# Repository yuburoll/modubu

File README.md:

# modubu

[한국어 설명은 이곳에서 보실 수 있습니다](README_ko.md)

semi-staggered(half row staggered, half column staggered) 38 key split keyboard under 100x100mm PCB

The name "modubu" is tofu square in Korean.

Started idea on my old sketch and [KeeNoard](https://github.com/yuburoll/KeeNoard), finished and polished the idea thanks to the great [DYA Dash](https://cormoran.github.io/dya-dash-keyboard/).

(Really surprisingly, I made this similar layout when I don't know about DYA Dash.)

credit for 우주신제품(wujusinjepum), the anonymous who named this keyboard.

## Preparation

- 2x rp2040 zero (boards formly created by waveshare) (Approx. 4-8$)

- 2x modubu PCB Boards (5 boards are 2$ on JLC w/o shipping cost)

- 1x printed case sets, 6 parts total (Approx. 12$ if you buy printed one on JLC)

- 38x diodes (Approx. 1$)

- 22x M2x6 screws, flathead (Approx. 1$)

- 2x PJ320A 1/8(3.5mm) TRRS connector (Approx. 1$)

- 1x 1/8(3.5mm) TRRS cable (Approx. 2$, may TRS cable can take the place.)

- 38x MX Hotswap Sockets (Approx. 4$) (or, use soldering version)

- 38x MX Keyswitches & Keycaps (Maybe this cost varies too much. 10$ on average)

Approx. 37-41$(w/o shipping cost) needed to build one.

## Default Keymap

Holding the key triggers front legend.

There is three layers - Num, Mouse, Fn - which can be noticed by the color legends. ◇ Means Transparent; which uses base keymap.

## Build Guides

work in progress. sorry!

You can see the images in the folder, which uploaded for build guides. Especially you may see how to solder the controller board, because this uses surface mounting by castelated pins.

This uses [qmk](https://qmk.fm/) to build the firmware. Copy "modubu" folder which is in "firmware/qmk" directory to "qmk_firmware\keyboards" folder, and build it via qmk msys.

Or, simply flash uf2 in "uf2Examples" folder by changing rp2040 zero in dfu mode, which can be executed by holding boot button while plugging in usb c. Vial versions are also prepared.

## Notes

(from my reddit reply) 

I made this keyboard for very local and ethnic layouts - Especially Koreans.

Koreans have lots of vowels, so we use left hand for consonants and right hand for vowels. The tragedy starts from here: B position is vowel(ㅠ, yu) in Korean keyboard, so very lots of Korean typers press B in right hand, still they use B in left hand when they typing English words.

Many Korean split ergo keyboard users literally suffers with B position problem; and this is one of most stiff learning curve of them. Some exchanges semicolon to B key, some slides the bottom row or have double B (zxcvbnm,./ => /zxcvbnm,. or zxcvbbnm,.) and some just get used to it.

And after the B, Koreans type many word like CamelCaseVariables (eg. past sentence "있었습니다(it-sut-SOUP-nee-da)" types like "dlTdjTtmqslek") - which make home row mods very cumbersome. We may have seperated shift key for this.

So that's why I made row stagger split design with additional keys: But I was surprised that I'm not the first one with this idea and layout.

## Licenses

all codes follow MIT license.

all designs and the hardware board follow CC BY-SA 4.0 license.

If you want to make a commercial product, it would be appreciated if you sponsor some bucks for me.

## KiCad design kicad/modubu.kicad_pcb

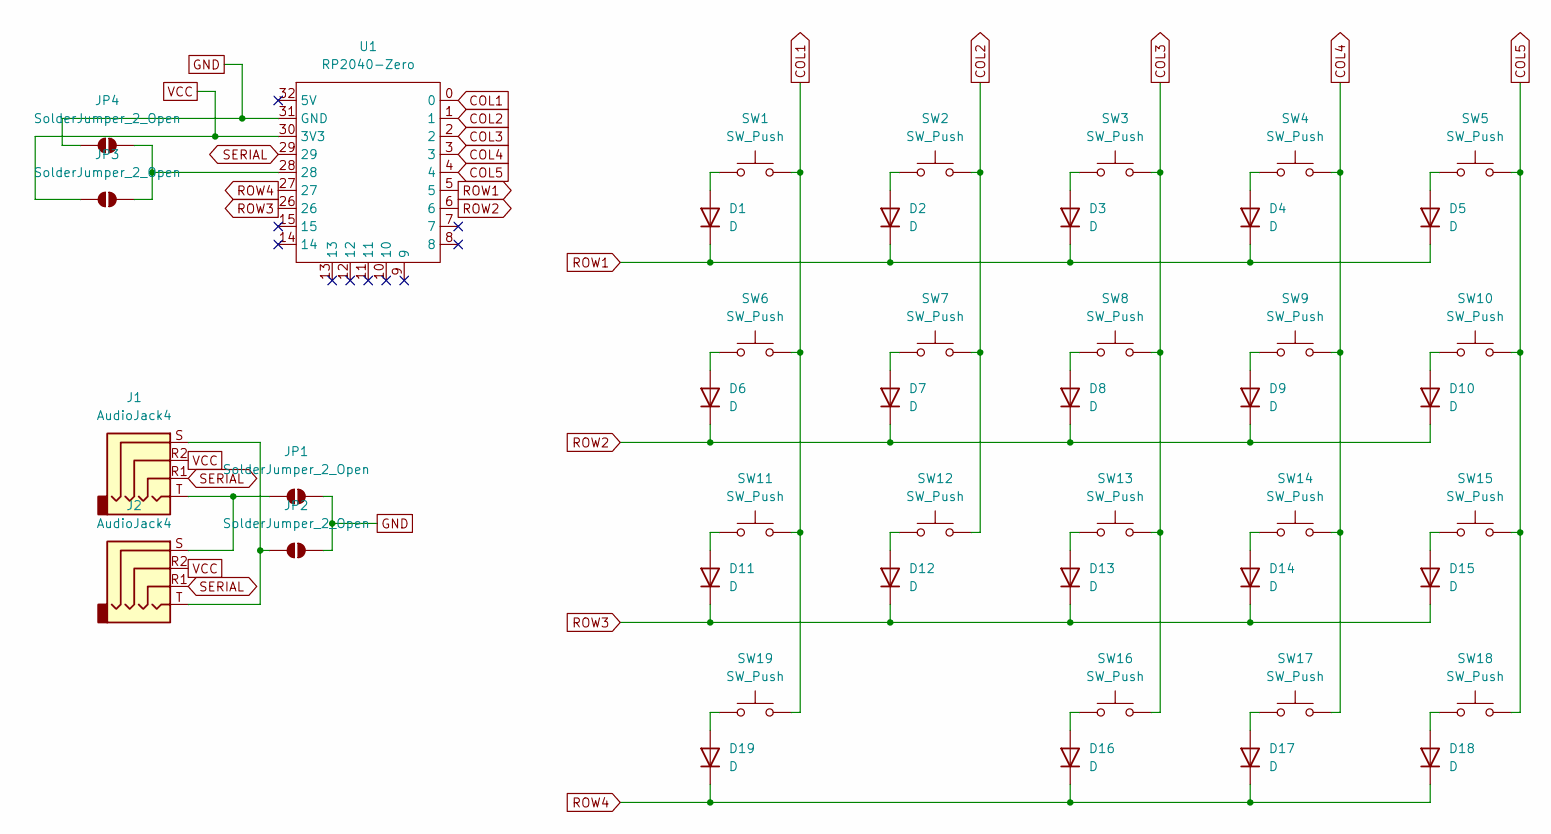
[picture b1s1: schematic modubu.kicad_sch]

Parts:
D1, D2, D3, D4, D5, D6, D7, D8, D9, D10, D11, D12, D13, D14, D15, D16, D17, D18, D19: D
J1, J2: AudioJack4
JP1, JP2, JP3, JP4: SolderJumper_2_Open
SW1, SW2, SW3, SW4, SW5, SW6, SW7, SW8, SW9, SW10, SW11, SW12, SW13, SW14, SW15, SW16, SW17, SW18, SW19: SW_Push
U1: RP2040-Zero

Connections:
COL1: SW1.2, SW6.2, SW11.2, SW19.2, U1.0
COL2: SW2.2, SW7.2, SW12.2, U1.1
COL3: SW3.2, SW8.2, SW13.2, SW16.2, U1.2
COL4: SW4.2, SW9.2, SW14.2, SW17.2, U1.3
COL5: SW5.2, SW10.2, SW15.2, SW18.2, U1.4
GND: JP1.2 (B), JP2.2 (B), JP4.1 (A), U1.31 (GND)
unnamed: D1.2 (A), SW1.1
unnamed: D2.2 (A), SW2.1
unnamed: D3.2 (A), SW3.1
unnamed: D4.2 (A), SW4.1
unnamed: D5.2 (A), SW5.1
unnamed: D6.2 (A), SW6.1
unnamed: D7.2 (A), SW7.1
unnamed: D8.2 (A), SW8.1
unnamed: D9.2 (A), SW9.1
unnamed: D10.2 (A), SW10.1
unnamed: D11.2 (A), SW11.1
unnamed: D12.2 (A), SW12.1
unnamed: D13.2 (A), SW13.1
unnamed: D14.2 (A), SW14.1
unnamed: D15.2 (A), SW15.1
unnamed: D16.2 (A), SW16.1
unnamed: D17.2 (A), SW17.1
unnamed: D18.2 (A), SW18.1
unnamed: D19.2 (A), SW19.1
unnamed: J1.T, J2.S, JP1.1 (A)
unnamed: J1.S, J2.T, JP2.1 (A)
unnamed: JP3.2 (B), JP4.2 (B), U1.28
ROW1: D1.1 (K), D2.1 (K), D3.1 (K), D4.1 (K), D5.1 (K), U1.5
ROW2: D6.1 (K), D7.1 (K), D8.1 (K), D9.1 (K), D10.1 (K), U1.6
ROW3: D11.1 (K), D12.1 (K), D13.1 (K), D14.1 (K), D15.1 (K), U1.26
ROW4: D16.1 (K), D17.1 (K), D18.1 (K), D19.1 (K), U1.27
SERIAL: J1.R1, J2.R1, U1.29
VCC: J1.R2, J2.R2, JP3.1 (A), U1.30 (3V3)

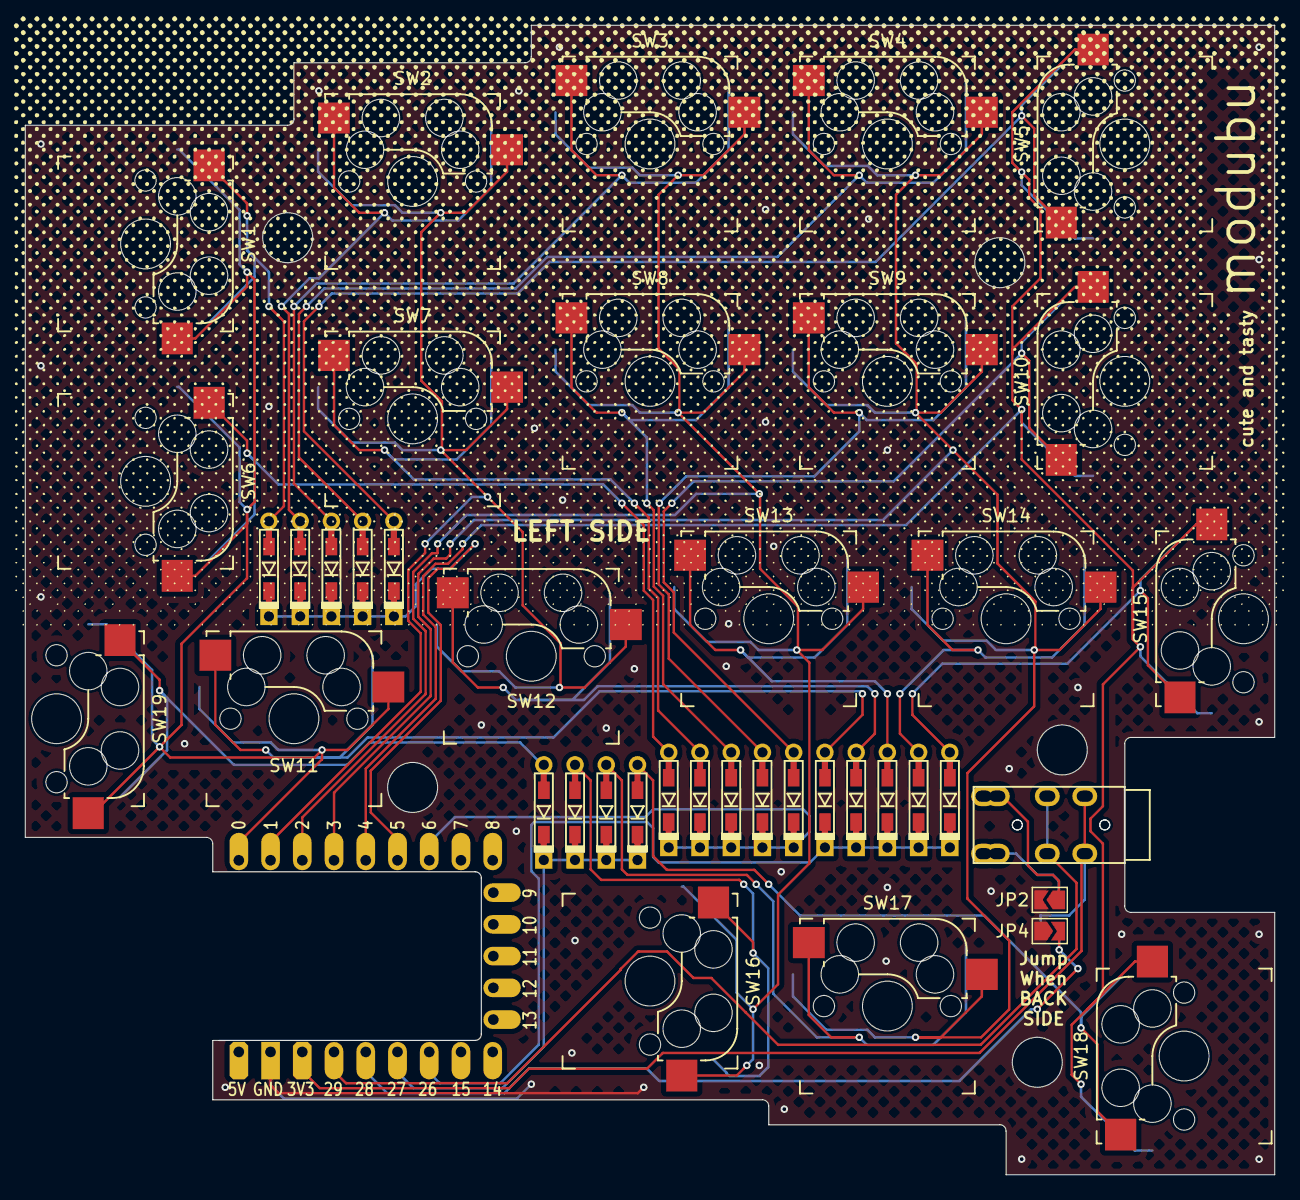
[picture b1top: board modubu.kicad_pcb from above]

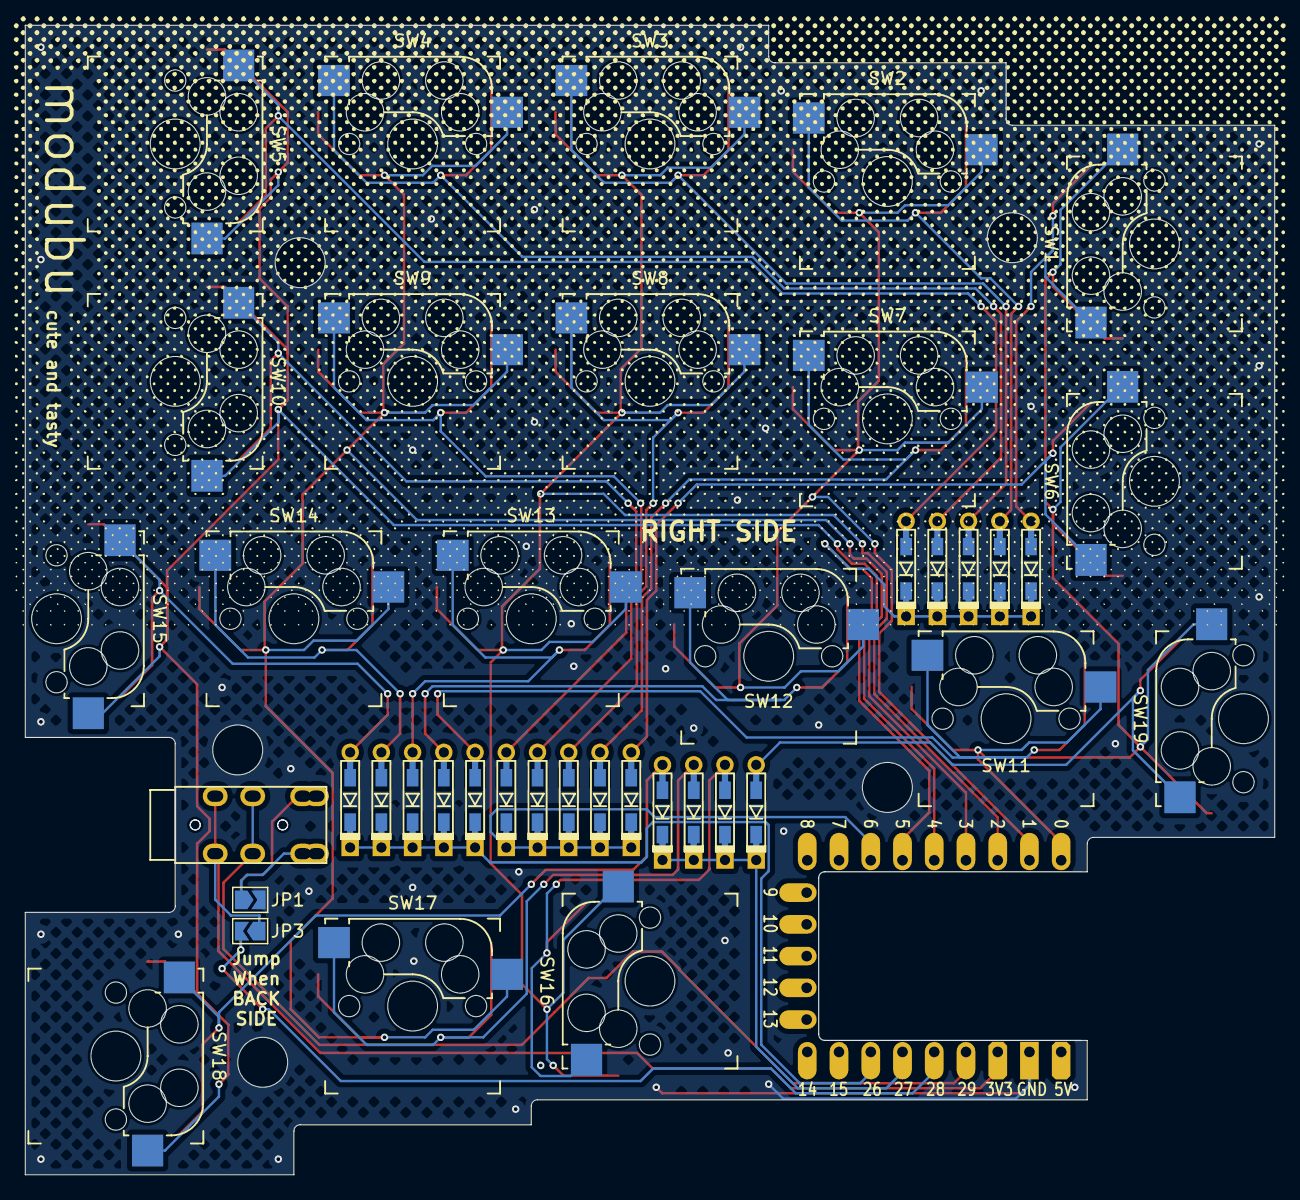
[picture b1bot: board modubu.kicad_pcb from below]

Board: 2 copper layers, 99.9 x 91.9 mm, 45 parts (3 on the bottom side), 34 nets.

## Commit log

2025-11-14 first upload
2025-11-14 add cc-by-sa
2025-11-14 fix firmware and upload examples
2025-11-14 upload case design
2025-11-21 update case failure
2025-11-21 edited keymaps
2025-11-21 update keymap
2025-11-21 keymap fix
2025-11-21 finalize default keymap
2025-11-22 add numpad keymap
2025-11-22 optimize keymap again
2025-11-22 another keymap polish
2025-11-22 upload vial version
2025-11-22 upload images
2025-11-22 add default keymap and move previous to combo
2025-11-24 add bumpon place to case
2025-11-25 add position silkscreen
2025-11-25 add korean buildguide
2025-11-25 image edit
2025-11-25 update default keymap
2025-11-26 update case design
2025-11-26 add keymap image
2025-11-26 upload soldering board - sundubu
2025-11-27 edit gerber ground via
2025-11-27 polish keymap
2025-11-27 add board art
2025-11-27 polish up board art
2025-11-28 update artwork
2025-11-28 update case for fdm minimal requirement
2025-11-29 add vial keymap example
2025-11-29 case update+tenting for mesh backplate
2025-11-30 migrated combo keymap to vial
2025-12-04 update new keymap
2025-12-07 add leafspring case
2025-12-07 add top mount case
2025-12-08 edit leafspring and remove topmount
    felt meaningless over test
2025-12-08 upload hexmesh backplate for leafspring
2025-12-08 hotfix hole of leafspring hexmash
2025-12-08 plate unit preservation edit
2025-12-09 fix error on numcombo.vil
2025-12-10 upload viki case
